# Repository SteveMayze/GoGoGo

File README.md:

# GoGoGo
Motor driver module for the Roll With It Project.

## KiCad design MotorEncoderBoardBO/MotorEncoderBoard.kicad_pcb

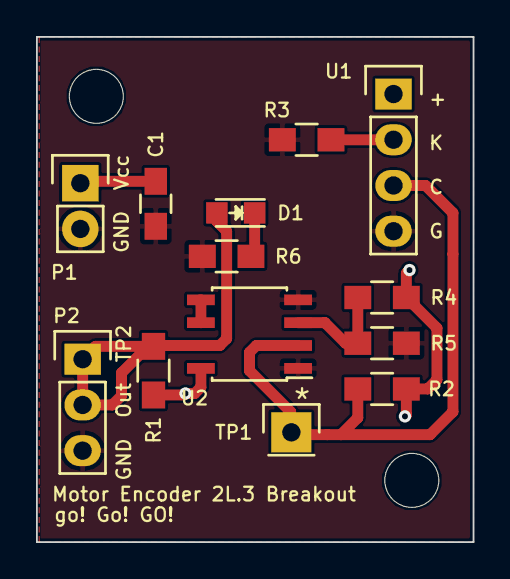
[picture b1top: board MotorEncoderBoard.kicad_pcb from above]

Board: 2 copper layers, 24.3 x 28.1 mm, 13 parts (0 on the bottom side), 8 nets.

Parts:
C1: 10u; C_0805_HandSoldering
D1: Led_Small; LED_0805
P1: PWR; Pin_Header_Straight_1x02
P2: CONN_01X03; Pin_Header_Straight_1x03
R1, R4, R5: 1K; R_0805_HandSoldering
R2: 10K; R_0805_HandSoldering
R3: 100; R_0805_HandSoldering
R6: 470; R_0805_HandSoldering
TP1: OptoOut; Pin_Header_Straight_1x01
U1: RPI-579N1; Pin_Header_Straight_1x04
U2: LM311D; SOIC-8_3.9x4.9mm_Pitch1.27mm

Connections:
/OptoOut: R2.2, TP1.1, U1.3, U2.2
/Output: D1.2, P2.1, P2.2, R1.2, U2.7
GND: C1.2, P1.2, P2.3, R3.2, R5.2, R6.2, U1.4, U2.1, U2.4
unnamed: D1.1, R6.1
unnamed: R3.1, U1.2
unnamed: R4.2, R5.1, U2.3
unnamed: U2.5, U2.6
VCC: C1.1, P1.1, R1.1, R2.1, R4.1, U1.1, U2.8

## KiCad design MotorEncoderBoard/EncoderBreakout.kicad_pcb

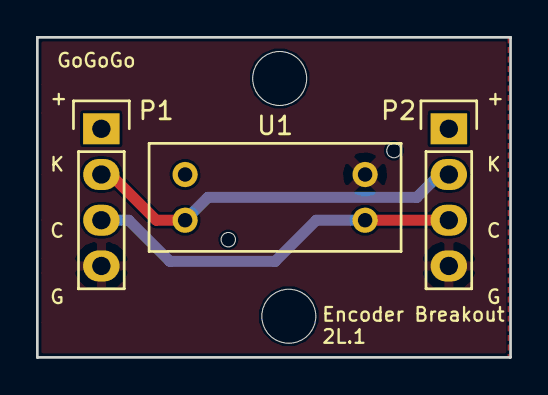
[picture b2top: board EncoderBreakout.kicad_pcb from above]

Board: 2 copper layers, 26.3 x 17.8 mm, 3 parts (0 on the bottom side), 4 nets.

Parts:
P1, P2: CONN_01X04; Pin_Header_Straight_1x04
U1: RPI-579N1

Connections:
/Cathode: P1.2, P2.2, U1.2
/Collector: P1.3, P2.3, U1.3
/GND: P1.4, P2.4, U1.4
/Vcc: P1.1, P2.1, U1.1

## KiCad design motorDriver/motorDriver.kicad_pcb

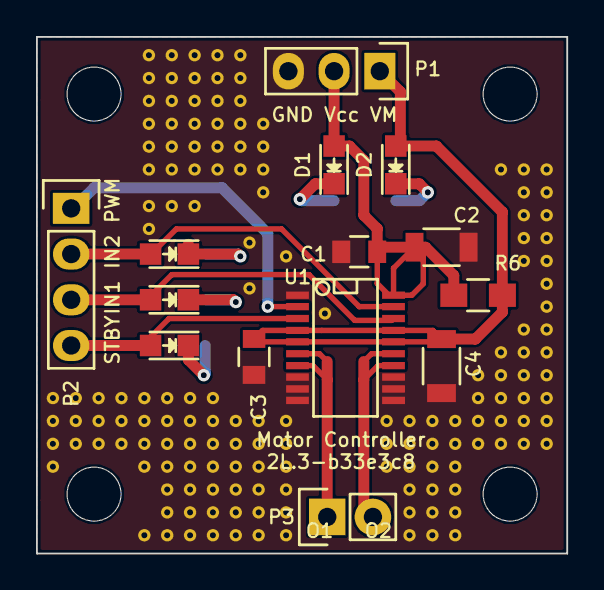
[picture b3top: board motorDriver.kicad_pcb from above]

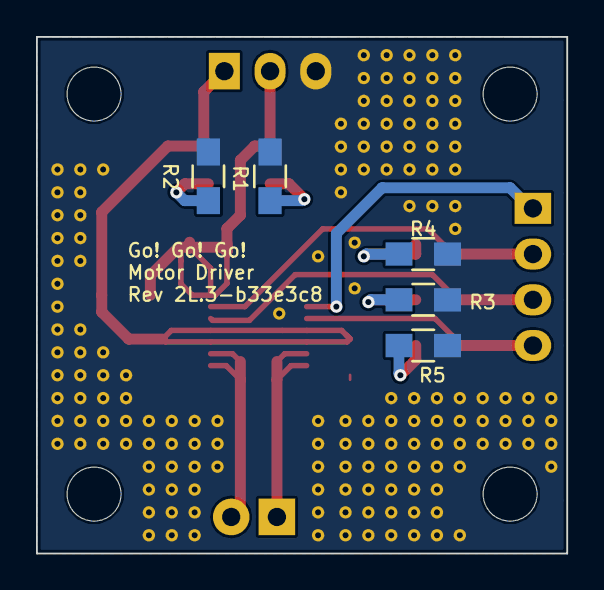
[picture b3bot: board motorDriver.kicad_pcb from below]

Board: 2 copper layers, 29.5 x 28.7 mm, 19 parts (5 on the bottom side), 14 nets.

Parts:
C1, C3: 0.1u; C_0805
C2, C4: 10u; C_1206
D1, D2, D3: LED; LED-0805
IN1, IN2: LED; LED-0805
P1: CONN_01X03; Pin_Header_Straight_1x03
P2: Input; Pin_Header_Straight_1x04
P3: Output; Pin_Header_Straight_1x02
R1, R2, R3, R4, R5: 1KΩ; R_0805_HandSoldering
R6: 0Ω; R_0805_HandSoldering
U1: TB6593FNG; SSOP-20

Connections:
/IN1: IN1.2, P2.3, U1.18
/IN2: IN2.2, P2.2, U1.19
/O1: P3.1, U1.6, U1.7
/O2: P3.2, U1.14, U1.15
/PMW: P2.1, U1.2
/STBY: D3.2, P2.4, U1.3
/VM: C3.1, C4.1, D2.2, P1.1, R6.2, U1.4, U1.5, U1.16, U1.17
/Vcc: C1.1, C2.1, D1.2, P1.2, R6.1, U1.20
GND: C1.2, C2.2, C3.2, C4.2, P1.3, R1.2, R2.2, R3.2, R4.2, R5.2, U1.1, U1.8, U1.9, U1.10, U1.11, U1.12, U1.13
unnamed: D1.1, R1.1
unnamed: D2.1, R2.1
unnamed: D3.1, R5.1
unnamed: IN1.1, R3.1
unnamed: IN2.1, R4.1

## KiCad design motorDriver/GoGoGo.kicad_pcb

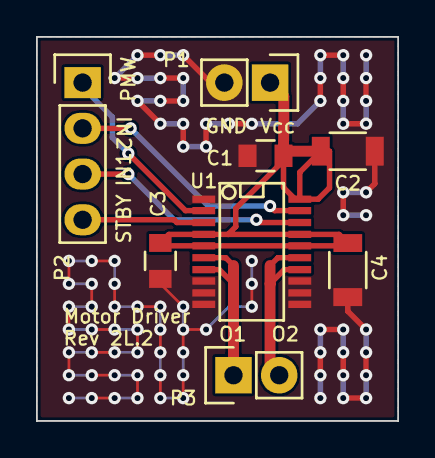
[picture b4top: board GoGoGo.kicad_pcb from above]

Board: 2 copper layers, 20.1 x 21.3 mm, 8 parts (0 on the bottom side), 8 nets.

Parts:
C1, C3: 0.1u; C_0805
C2, C4: 10u; C_1206
P1: Vcc; Pin_Header_Straight_1x02
P2: Input; Pin_Header_Straight_1x04
P3: Output; Pin_Header_Straight_1x02
U1: TB6593FNG; SSOP-20

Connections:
/IN1: P2.3, U1.18
/IN2: P2.2, U1.19
/O1: P3.1, U1.6, U1.7
/O2: P3.2, U1.14, U1.15
/PMW: P2.1, U1.2
/STBY: P2.4, U1.3
/VM: C1.1, C2.1, C3.1, C4.1, P1.1, U1.4, U1.5, U1.16, U1.17, U1.20
GND: C1.2, C2.2, C3.2, C4.2, P1.2, U1.1, U1.8, U1.9, U1.10, U1.11, U1.12, U1.13

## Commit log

2015-06-15 Initial checkin
2015-06-15 Schemantic done
2015-06-15 Initial layout
2015-06-16 Main layout done
2015-06-16 Gerbers created
2015-06-27 Motor encoder board inital checking
2015-06-28 Schematic done
2015-06-28 Layout for motor encoder board done
2015-06-28 Added the encoder wheel
2015-07-01 Combined the motor controller and encoder onto one board
2015-07-30 Made corrections to the board based on the video on testing
2015-08-01 Added a small correction to a route
2015-08-01 Correction to the motor encoder board
2015-08-01 Added some images of the output and setup
2015-08-03 Regenerated Gerbers for new boards and stensils
2015-08-04 Added changed the 100Ohm to 10kOhm for the sense resistor
2015-08-29 Update to circuit
2015-08-29 Final corrections after testing
2015-09-26 Added firmware and test results
2015-09-29 Testing firmware and results
2015-10-05 Renamed kicad to motorDriver
2015-10-05 Renamed the GoGoGo files to motorDriver
2015-10-05 Updated layout for Rev 2
2015-10-05 Generated Gerbers for Rev2
2015-10-05 Shifted the title label to the back
2015-10-21 Corrected a stitching via on ground pins
2015-11-27 Gerbers and small label changes
2015-11-27 Removed some stitch vias from near other footprints
2015-12-23 Encoder wheel design update
2015-12-25 Updated the encoder wheel design for smaller slots
2015-12-28 Added a default speed to the SteeringTest2 as well as immediate stop signals
2015-12-28 Started the writeup for the Go, Go, Go!
2016-01-08 Test results and wheel design changes
2016-01-08 Created the version b of rev 4 and 5 and created the appropriate SVG files
2016-01-10 Testing of the new wheel revisions
2016-01-10 Added the annotated saleae image to show the artifacts
2016-01-10 moved some files around
2016-01-10 Added some images etc for the build log
2016-01-16 Created the revision 6 of the encoder wheel - 0.5mm slots
2016-04-19 Created the encorder breakout
2016-04-21 Copied the Encoder Board to a new directory to start a break-out version. Created Gerbers and ordered the board 2L.3Breakout
2016-04-22 Removed the breakout artifacts from the MotorEncoderBoard directory
2016-04-25 Tentative location for LED
2016-04-25 New changes to the test firmware
2016-04-25 Updated the repo and recorded the WhileWheel.log
2016-04-25 Removed unwanted files
2016-05-08 Added the basic transfer-to-nucleo code.
2016-05-16 Added more code for testing the wheels
2016-05-17 Added indicator LED
2016-05-20 Enhanced the board with indicator LEDs
2016-05-20 Interrum save of nucleo conversion code
2016-06-04 Firmware for the Nucleo - with small test case for both wheels
2016-06-20 Changed the port/pin assignments from Nucleo to Central Command
2016-06-20 Added the fix for the system clock as per Ron's testing the clock CC video
2016-06-22 Created the a runCommand function to enable a type of scripting of motions
2016-07-05 Added a crude synchronisation mechanism for the wheels
2016-07-06 Tried tuning the compensating code a bit. There are still many variables to sort out
2016-10-29 RWI57 - A refactoring pass to move on - Created the Wheel.c/h
2016-10-29 RWI48 - Ceedlin & Unity to TDD Wheel Code
2016-10-29 RWI49 - TTDing the Straight Code ( & continued)
2016-10-30 RWI49: Broke out the Delegated IRQ handler to its own class
2016-10-30 RWI49 - Exposed the delegate_left/rightCounters
2016-11-01 Added the tests for the Wheel API
